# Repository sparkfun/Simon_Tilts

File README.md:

Simon Tilts - Through Hole Soldering Kit
========================================

[  
*Simon Tilts - Through Hole Soldering (KIT-12634)*](https://www.sparkfun.com/products/12634)

This is a new take on the original Simon Says game. Instead of pressing buttons, the player is challenged to tilt the game in a specific pattern of rotations.

Repository Contents
-------------------

* **/Firmware** - Source code, an Arduino Sketch
* **/Hardware** - Eagle design files (Schematic and Board)

License Information
-------------------
The hardware is released under [Creative Commons Share-alike 3.0](http://creativecommons.org/licenses/by-sa/3.0/).  
The firmware is released under beerware license

Hardware author: Pete Lewis @ SparkFun Electonics  
Firmware original author: Pete Lewis @ SparkFun Electronics

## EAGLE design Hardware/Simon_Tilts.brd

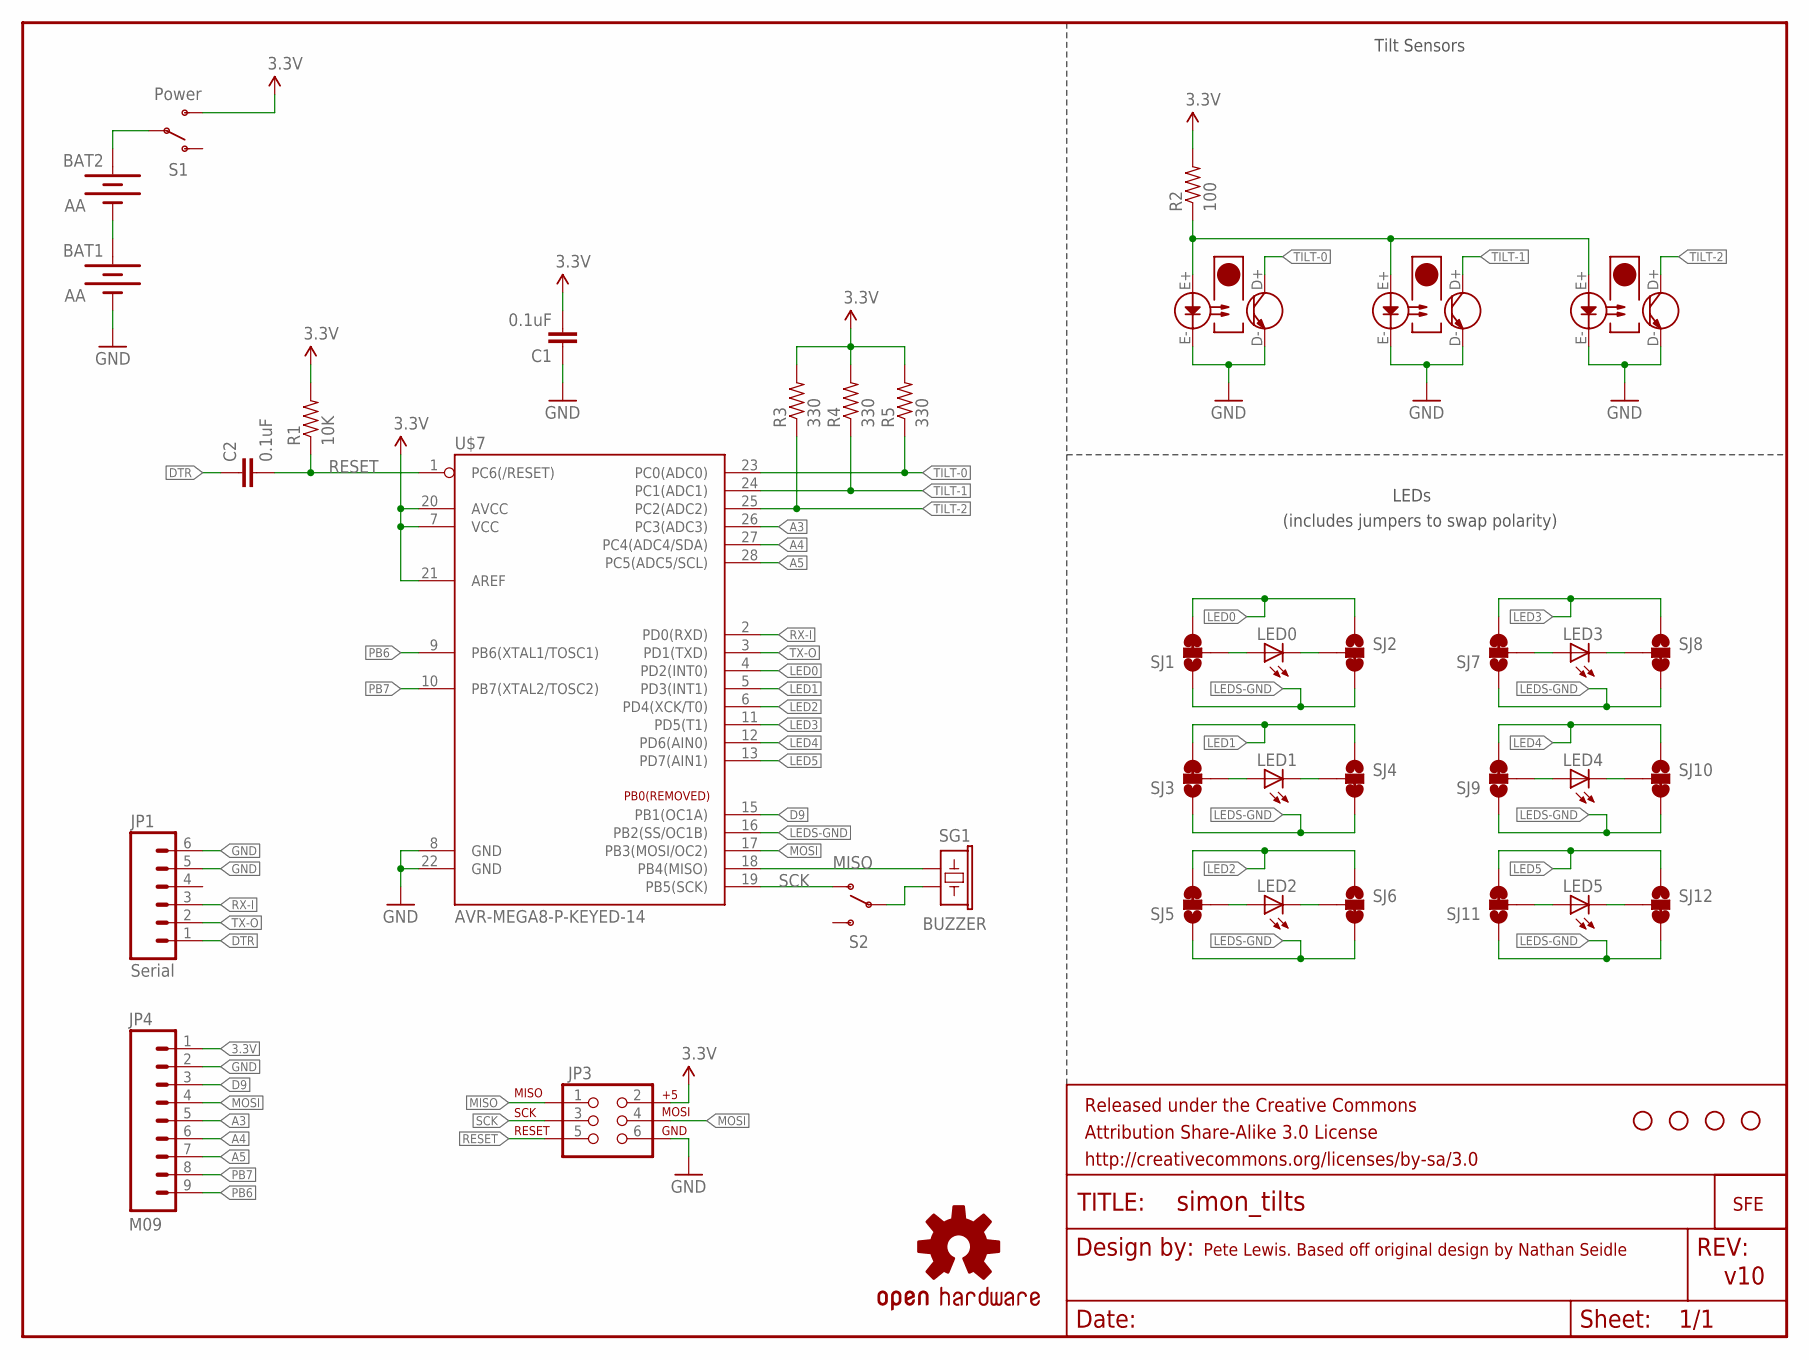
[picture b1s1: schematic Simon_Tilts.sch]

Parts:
BAT1, BAT2: AA; BATTERY-AA-KIT
C1, C2: 0.1uF; CAP-PTH-SMALL-KIT
FRAME1: FRAME-LETTER; CREATIVE_COMMONS
JP1: Serial; 1X06-NOSILK
JP2, JP5, JP6, JP7: STAND-OFF
JP3: AVR_SPI_PRG_6NS; 2X3-NS
JP4: M09; 1X09
LED0, LED1, LED2, LED3, LED4, LED5: LED5MM-KIT
R1: 10K; AXIAL-0.3-KIT
R2: 100; AXIAL-0.3-KIT
R3, R4, R5: 330; AXIAL-0.3-KIT
S1: Power; SWITCH-SPDT_KIT
S2: SWITCH-SPDTKIT; SWITCH-SPDT_KIT
SG1: BUZZER; BUZZER-12MM-KIT
SJ1, SJ2, SJ3, SJ4, SJ5, SJ6, SJ7, SJ8, SJ9, SJ10, SJ11, SJ12: SOLDERJUMPER_2WAYS; SJ_3
U$1: LOGO-SFENEW; SFE-NEW-WEBLOGO
U$3: OSHW-LOGOS; OSHW-LOGO-S
U$4, U$5, U$6: TILT_SENSORV5; TILT_SENSOR_V5
U$7: AVR-MEGA8-P-KEYED-14; DIL28-3_KEYED-14

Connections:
3.3V: C1.2, JP3.2, JP4.1, R1.P$2 (2), R2.P$2 (2), R3.P$2 (2), R4.P$2 (2), R5.P$2 (2), S1.3 (S), U$7.7 (VCC), U$7.20 (AVCC), U$7.21 (AREF)
A3: JP4.5, U$7.26 (PC3(ADC3))
A4: JP4.6, U$7.27 (PC4(ADC4/SDA))
A5: JP4.7, U$7.28 (PC5(ADC5/SCL))
D9: JP4.3, U$7.15 (PB1(OC1A))
DTR: C2.1, JP1.1
GND: BAT1.GND@1 (-), C1.1, JP1.5, JP1.6, JP3.6, JP4.2, U$4.D-, U$4.E-, U$5.D-, U$5.E-, U$6.D-, U$6.E-, U$7.8 (GND), U$7.22 (GND)
LED0: SJ1.3, SJ2.1, U$7.4 (PD2(INT0))
LED1: SJ3.3, SJ4.1, U$7.5 (PD3(INT1))
LED2: SJ5.3, SJ6.1, U$7.6 (PD4(XCK/T0))
LED3: SJ7.3, SJ8.1, U$7.11 (PD5(T1))
LED4: SJ9.3, SJ10.1, U$7.12 (PD6(AIN0))
LED5: SJ11.3, SJ12.1, U$7.13 (PD7(AIN1))
LEDS-GND: SJ1.1, SJ2.3, SJ3.1, SJ4.3, SJ5.1, SJ6.3, SJ7.1, SJ8.3, SJ9.1, SJ10.3, SJ11.1, SJ12.3, U$7.16 (PB2(SS/OC1B))
MISO: JP3.1, SG1.+ (1), U$7.18 (PB4(MISO))
MOSI: JP3.4, JP4.4, U$7.17 (PB3(MOSI/OC2))
unnamed: LED0.A, SJ1.2
unnamed: BAT2.PWR@1 (+), S1.2
unnamed: S2.2, SG1.- (2)
unnamed: BAT1.PWR@1 (+), BAT2.GND@1 (-)
unnamed: R2.P$1 (1), U$4.E+, U$5.E+, U$6.E+
unnamed: LED0.K (C), SJ2.2
unnamed: LED1.A, SJ3.2
unnamed: LED1.K (C), SJ4.2
unnamed: LED2.A, SJ5.2
unnamed: LED2.K (C), SJ6.2
unnamed: LED3.A, SJ7.2
unnamed: LED3.K (C), SJ8.2
unnamed: LED4.A, SJ9.2
unnamed: LED4.K (C), SJ10.2
unnamed: LED5.A, SJ11.2
unnamed: LED5.K (C), SJ12.2
PB6: JP4.9, U$7.9 (PB6(XTAL1/TOSC1))
PB7: JP4.8, U$7.10 (PB7(XTAL2/TOSC2))
RESET: C2.2, JP3.5, R1.P$1 (1), U$7.1 (PC6(/RESET))
RX-I: JP1.3, U$7.2 (PD0(RXD))
SCK: JP3.3, S2.1 (O), U$7.19 (PB5(SCK))
TILT-0: R5.P$1 (1), U$4.D+, U$7.23 (PC0(ADC0))
TILT-1: R4.P$1 (1), U$5.D+, U$7.24 (PC1(ADC1))
TILT-2: R3.P$1 (1), U$6.D+, U$7.25 (PC2(ADC2))
TX-O: JP1.2, U$7.3 (PD1(TXD))

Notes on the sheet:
v10
Pete Lewis. Based off original design by Nathan Seidle
Tilt Sensors
LEDs
(includes jumpers to swap polarity)

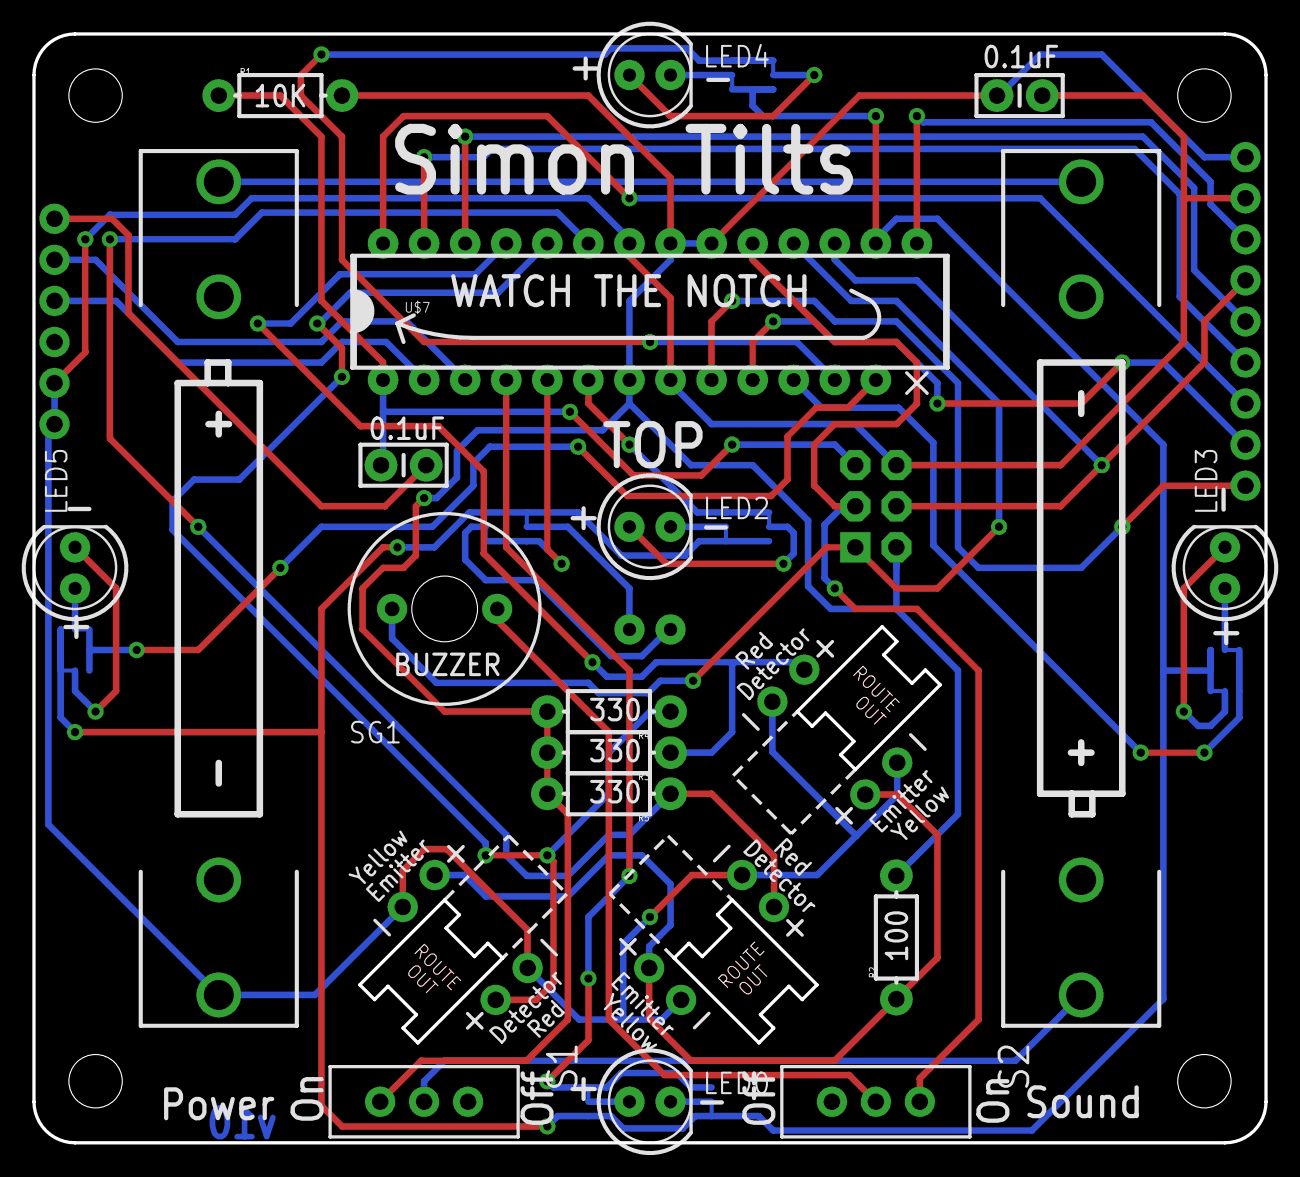
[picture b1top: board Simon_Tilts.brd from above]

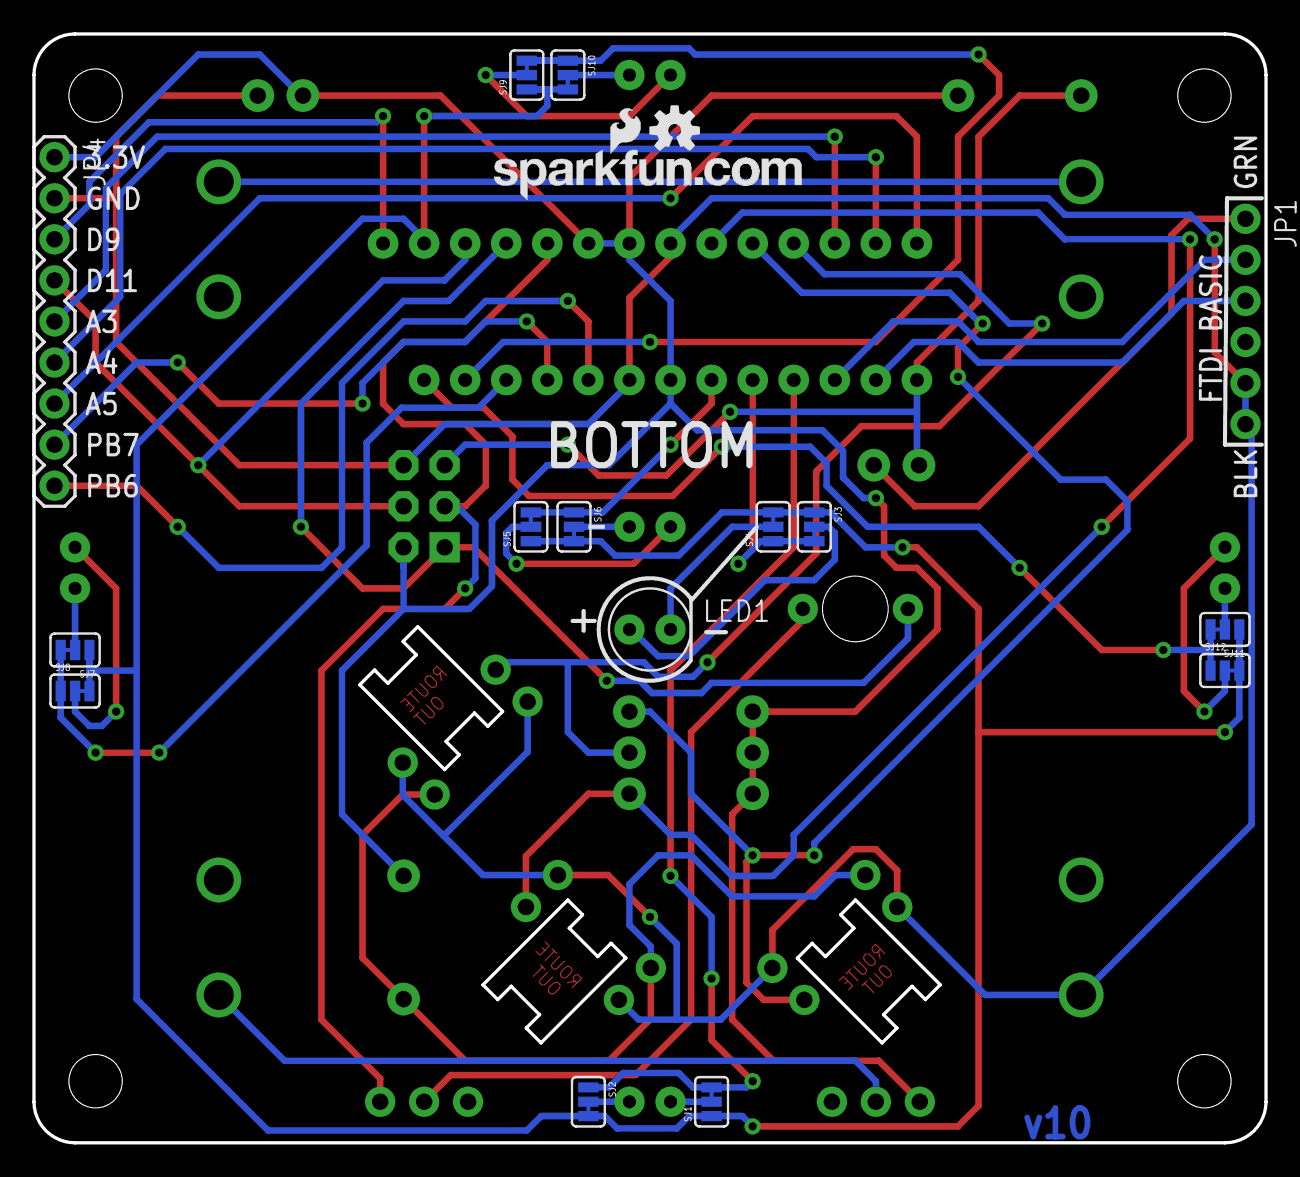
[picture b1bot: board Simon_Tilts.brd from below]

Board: 2 copper layers, 76.2 x 68.6 mm, 44 parts (18 on the bottom side), 41 nets.

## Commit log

2013-11-07 Initial commit of hardware, firmware, gitignore, and cleanup batch file
    Hardware v01 ready for protos
2013-11-25 ignoring "ods" BOMs
2013-11-25 V10 ready for red boards
    -Updated tilt sensor package to TILT_SENSOR_V5, then rerouted irregular
    traces.
    -Changed version to "V10" in bottom copper AND schematic.
2013-11-28 Updated game play rules
    added "waiting mode", the player must tilt the game in any way to engage
    starting the game.
    Also changed it so the first tilt is always a side LED, this is more
    intuitive for game play. This way you don't have to explain the "first
    tilt is free thing".
2014-01-03 Code cleanup
    -Added beerware
    -removed unnecessary comments
    -added more pertinent comments
    -cleaned up a ton of tabbing and spacing
    -removed a few un-used variables
2014-01-03 Update README.md
    now includes standard stuff like image, link, contents and author
2014-01-03 Update README.md
    updated firmware license to beerware
2014-01-09 Firmware cleanup
    A ton of re-organizing and commenting.
2014-01-09 Repo clean up
2014-01-09 Spell checked my comments :)
2014-01-10 fixing line widths
    about half way done
2014-01-13 line widths and more
    -Reduced remaining line widths of comments
    -Fixed comment about tilt sensor explanation (impossibilities) to 1 and
    6, (not 5 and 6)
    -changes comparisons to fail (a boolean variable ) to false/true rather
    than "0" and "1"
2025-06-27 Update README.md
    Updating link

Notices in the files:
parts and their libraries:
SparkFun-Connectors: Licensing: CC v3.0 Share-Alike You are welcome to use this library for commercial purposes.
SparkFun-Aesthetics: Released under the Creative Commons Attribution Share-Alike 3.0 License
SparkFun-Aesthetics: Released under the Creative Commons
